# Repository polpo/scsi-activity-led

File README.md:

# SCSI activity LED adapter #

Do you use a [BlueSCSI](https://github.com/erichelgeson/bluescsi) externally on your classic Macintosh? Do you wish the little hard drive activity light on the Mac still flashed when using it? This adapter will make that happen.

This adapter has been tested on a Macintosh SE and Macintosh SE/30. Your mileage may vary with other computers.

## Making the board ##

Submit the gerbers under the gerbers/ directory to your favorite PCB manufacturer. I made mine at [OSH Park](https://oshpark.com/shared_projects/9X7GausD). You can order at that link and as of the time of writing this README, it's only $1.20 for three PCBs!

A BOM is in the [bom.csv](bom.csv) file, consisting of:

- 74LVC1G14 Schmitt trigger logic inverter. I've specifically chosen the Nexperia 74LVC1G14GV,125 because the trigger voltages in its datasheet match the best with SCSI logic levels.
- 2- and 3-pin headers. The 2-pin header is keyed so it fits perfectly with the HD LED connector on the Macintosh SE and SE/30 in the proper orientation.
- One 150 ohm 1206 SMT resistor to limit current to the LED.

Soldering the SMT components shouldn't be too hard even if you don't have SMT soldering experience. Just use plenty of flux, place the parts, and touch the pads with a soldering iron coated with solder.

## Connecting the adapter ##

### 1. Connect to the proper SCSI pins ###

Use 3 dupont connectors to connect the adapter to the following pins on the Macintosh's internal SCSI port:

- TERMPWR: pin 26 - provides power to the adapter. Connect to TPWR on the adapter.
- GND: there are lots of ground pins. Just pick one, like pin 28 which is right next to TERMPWR. Connect to GND on the adapter.
- /BSY: pin 36 - this signal is low when the SCSI bus is in use, and high when the bus is free. Connect to BSY on the adapter.

### 2. Connect the HD activity LED ###

This should plug right in if you're using the LED connector on the Macintosh SE and SE/30.

### 4. Watch the blinkenlights! ###

Mount the adapter with some double-sided tape so the bottom doesn't short out on the computer's chassis. Turn it on and hopefully you will have a nicely blinking activity LED!

## TODO ##

- Design a foolproof version of the adapter that plugs directly into a 50-pin internal SCSI connector.
- Investigate how appropriate other signals on the SCSI bus are for activity lights. I've noticed that when no SCSI devices are connected, the Mac's SCSI controller toggles /BSY continuously, which is annoying.

## License ##

[The project license](LICENSE.txt) is under the CERN Open Hardware Licence Version 2 - Permissive.

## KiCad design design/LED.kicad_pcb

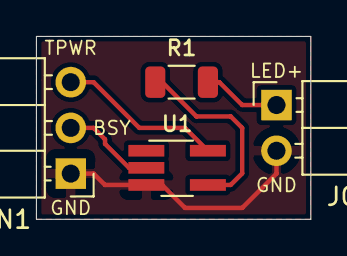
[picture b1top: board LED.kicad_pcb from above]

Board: 2 copper layers, 15.2 x 10.2 mm, 4 parts (0 on the bottom side), 5 nets.

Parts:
JIN1: Conn_01x03_Male; PinHeader_1x03_P2.54mm_Horizontal
JOUT1: Conn_01x02_Male; PinHeader_1x02_P2.54mm_Horizontal
R1: 150; R_1206_3216Metric
U1: 74AHC1G04; TSOT-23-5_HandSoldering

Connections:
GND: JIN1.1, JOUT1.2, U1.3
unnamed: JIN1.2, U1.2
unnamed: JOUT1.1, R1.1
unnamed: R1.2, U1.4
VCC: JIN1.3, U1.5

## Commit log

2022-04-11 Add images
2022-04-11 Add license
2022-04-11 Minor copy update, add TODO
2022-04-11 Link shared OSH Park project
2022-04-11 Better and more accurate connection images
2022-04-11 Add pin for BSY
2022-04-14 Add TODO to investigate alternatives to /BSY
